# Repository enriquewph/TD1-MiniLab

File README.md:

# TD1-MiniLab
Practico de Laboratorio N° 1. --- Mini Lab ---

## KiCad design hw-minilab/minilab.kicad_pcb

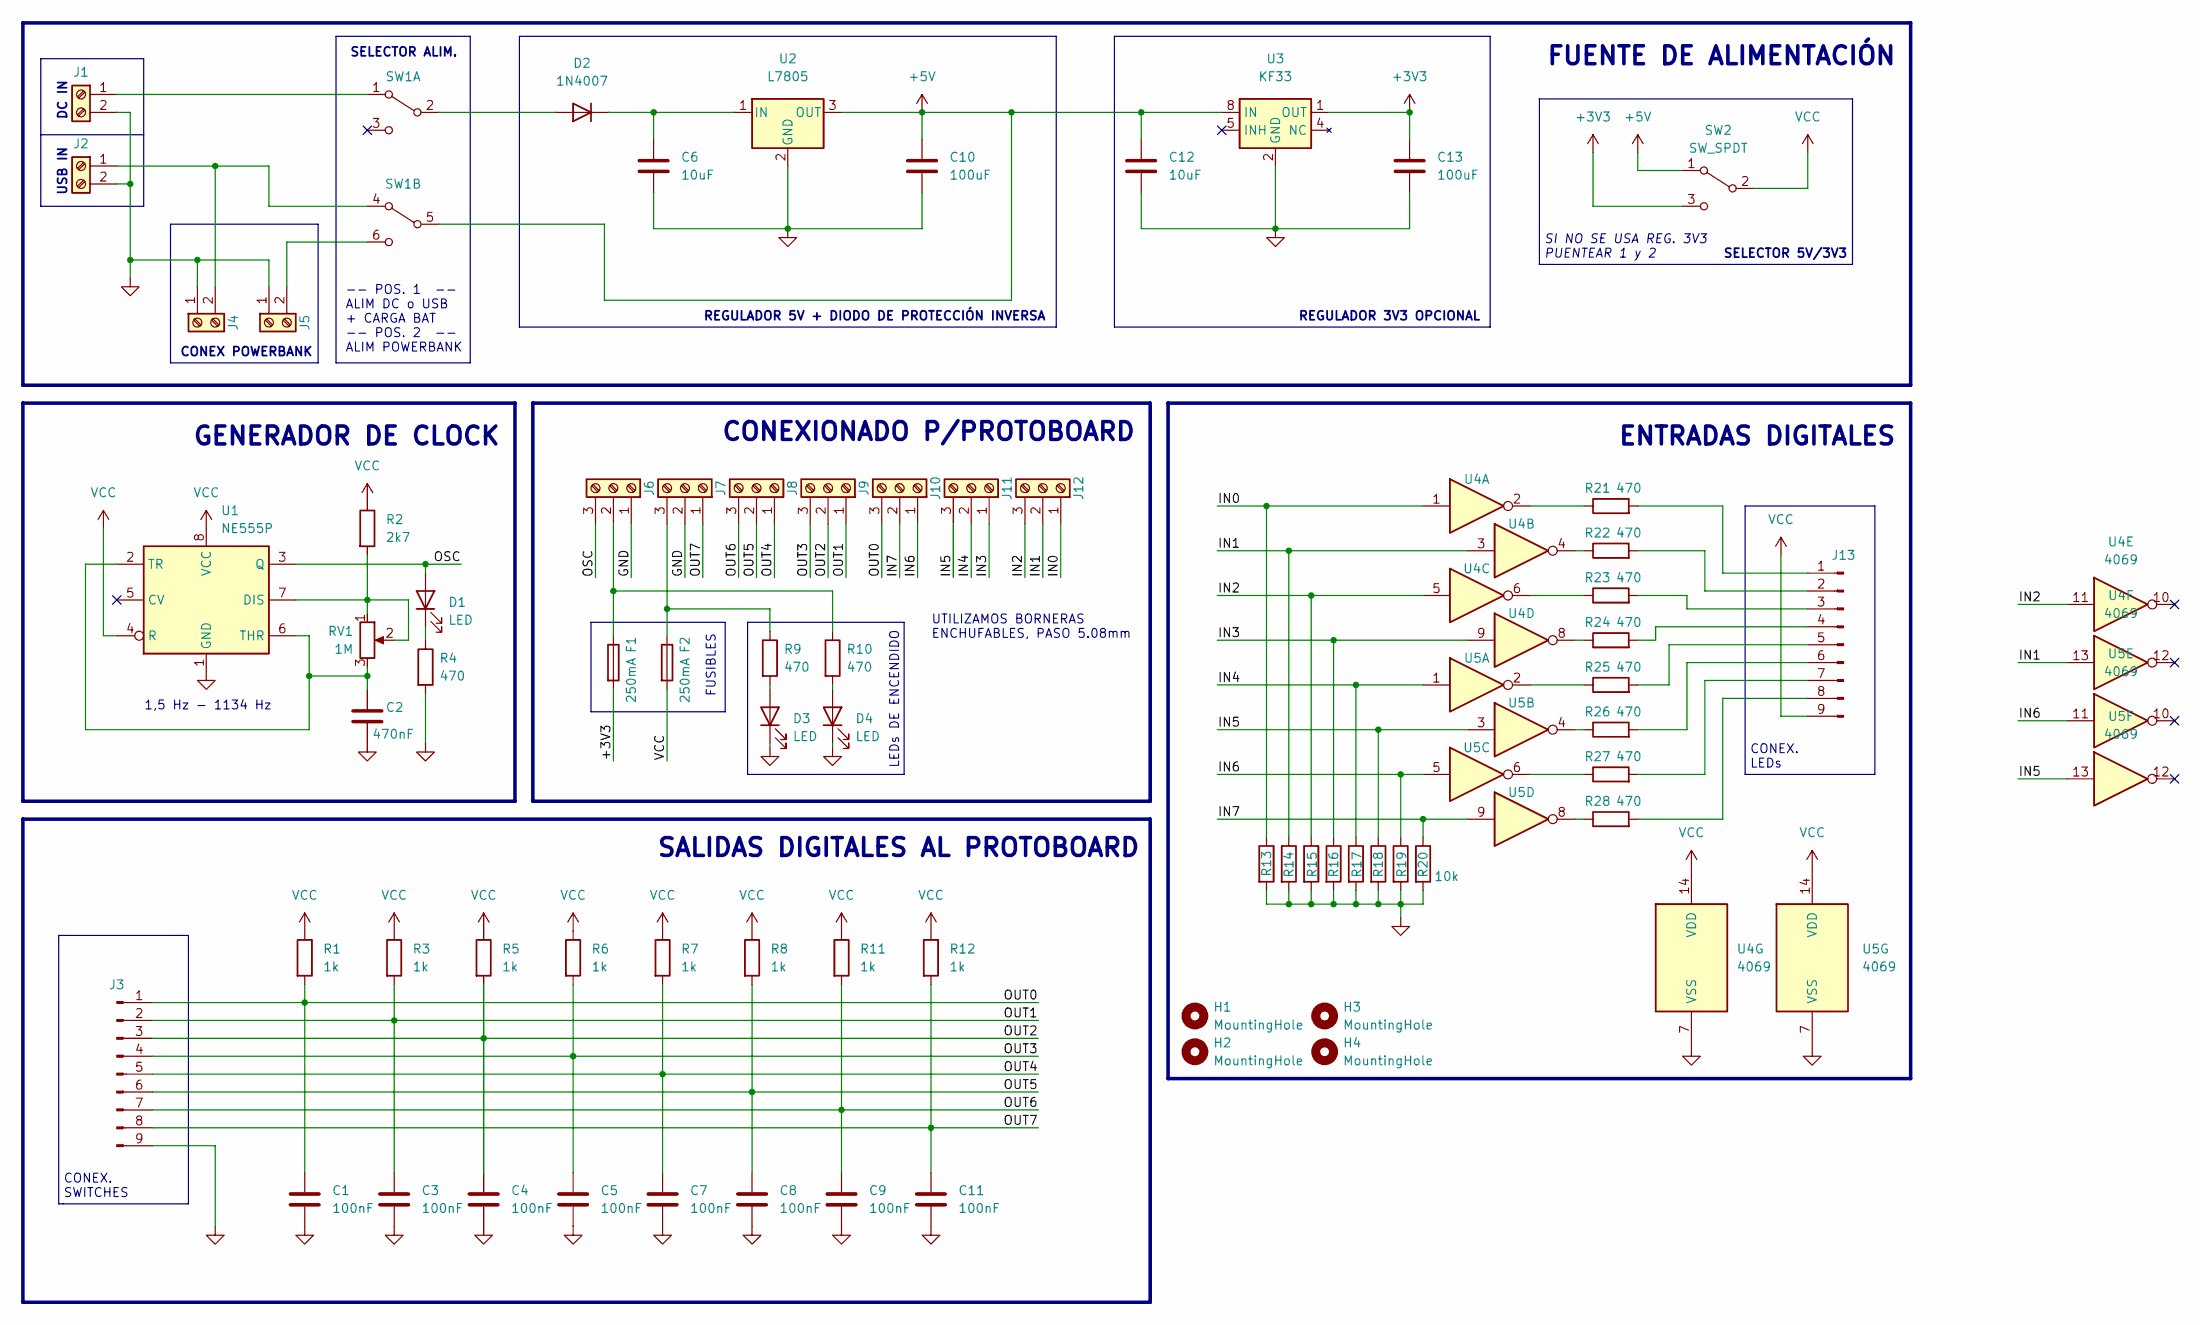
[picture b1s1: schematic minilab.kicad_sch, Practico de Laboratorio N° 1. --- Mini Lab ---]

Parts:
C1, C3, C4, C5, C7, C8, C9, C11: 100nF; C_Disc_D5.0mm_W2.5mm_P5.00mm
C2: 470nF; C_Disc_D5.0mm_W2.5mm_P5.00mm
C6, C12: 10uF; C_Disc_D5.0mm_W2.5mm_P2.50mm
C10, C13: 100uF; C_Disc_D5.0mm_W2.5mm_P2.50mm
D1, D3, D4: LED; PinHeader_1x02_P2.54mm_Vertical
D2: 1N4007; D_DO-41_SOD81_P10.16mm_Horizontal
F1, F2: 250mA; TestPoint_2Pads_Pitch5.08mm_Drill1.3mm
H1, H2, H3, H4: MountingHole; MountingHole_3.2mm_M3
J1, J2, J4, J5: Screw_Terminal_01x02; TestPoint_2Pads_Pitch5.08mm_Drill1.3mm
J3, J13: Conn_01x09_Male; PinHeader_1x09_P2.54mm_Vertical
J6, J7, J8, J9, J10, J11, J12: Screw_Terminal_01x03; TerminalBlock_RND_205-00288_1x03_P5.08mm_Horizontal
R1, R3, R5, R6, R7, R8, R11, R12: 1k; R_Axial_DIN0207_L6.3mm_D2.5mm_P7.62mm_Horizontal
R2: 2k7; R_Axial_DIN0207_L6.3mm_D2.5mm_P7.62mm_Horizontal
R4, R9, R10, R21, R22, R23, R24, R25, R26, R27, R28: 470; R_Axial_DIN0207_L6.3mm_D2.5mm_P7.62mm_Horizontal
R13, R14, R15, R16, R17, R18, R19, R20: 10k; R_Axial_DIN0207_L6.3mm_D2.5mm_P7.62mm_Horizontal
RV1: 1M; PinHeader_1x03_P2.54mm_Vertical
SW1: SW_DPDT_x2; TestPoint_6Pads_Pitch5.08mm_Drill1.3mm
SW2: SW_SPDT; TestPoint_3Pads_Pitch5.08mm_Drill1.3mm
U1: NE555P; DIP-8_W7.62mm_Socket_LongPads
U2: L7805; TO-220-3_Horizontal_TabUp
U3: KF33; SOIC-8-1EP_3.9x4.9mm_P1.27mm_EP2.29x3mm
U4, U5: 4069

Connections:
+3V3: C13.1, F1.2, SW2.3 (C), U3.1 (OUT)
+5V: C10.1, C12.1, SW1.5 (B), SW2.1 (A), U2.3 (OUT), U3.8 (IN)
/IN0: J12.1, R13.1, U4.1
/IN1: J12.2, R14.1, U4.3, U4.13
/IN2: J12.3, R15.1, U4.5, U4.11
/IN3: J11.1, R16.1, U4.9
/IN4: J11.2, R17.1, U5.1
/IN5: J11.3, R18.1, U5.3, U5.13
/IN6: J10.1, R19.1, U5.5, U5.11
/IN7: J10.2, R20.1, U5.9
/OSC: D1.2 (A), J6.3, U1.3 (Q)
/OUT0: C1.1, J3.1, J10.3, R1.2
/OUT1: C3.1, J3.2, J9.1, R3.2
/OUT2: C4.1, J3.3, J9.2, R5.2
/OUT3: C5.1, J3.4, J9.3, R6.2
/OUT4: C7.1, J3.5, J8.1, R7.2
/OUT5: C8.1, J3.6, J8.2, R8.2
/OUT6: C9.1, J3.7, J8.3, R11.2
/OUT7: C11.1, J3.8, J7.1, R12.2
GND: C1.2, C2.2, C3.2, C4.2, C5.2, C6.2, C7.2, C8.2, C9.2, C10.2, C11.2, C12.2, C13.2, D3.1 (K), D4.1 (K), J1.2, J2.2, J3.9, J4.1, J5.1, J6.1, J7.2, R4.2, R13.2, R14.2, R15.2, R16.2, R17.2, R18.2, R19.2, R20.2, U1.1 (GND), U2.2 (GND), U3.2 (GND), U3.3 (GND), U3.6 (GND), U3.7 (GND), U3.9 (GND), U4.7 (VSS), U5.7 (VSS)
unnamed: C2.1, RV1.3, U1.2 (TR), U1.6 (THR)
unnamed: C6.1, D2.1 (K), U2.1 (IN)
unnamed: D1.1 (K), R4.1
unnamed: D2.2 (A), SW1.2 (B)
unnamed: D3.2 (A), R9.2
unnamed: D4.2 (A), R10.2
unnamed: F1.1, J6.2, R10.1
unnamed: F2.1, J7.3, R9.1
unnamed: J1.1, SW1.1 (A)
unnamed: J2.1, J4.2, SW1.4 (A)
unnamed: J5.2, SW1.6 (C)
unnamed: J13.1, R21.2
unnamed: J13.2, R22.2
unnamed: J13.3, R23.2
unnamed: J13.4, R24.2
unnamed: J13.5, R25.2
unnamed: J13.6, R26.2
unnamed: J13.7, R27.2
unnamed: J13.8, R28.2
unnamed: R2.2, RV1.1, RV1.2, U1.7 (DIS)
unnamed: R21.1, U4.2
unnamed: R22.1, U4.4
unnamed: R23.1, U4.6
unnamed: R24.1, U4.8
unnamed: R25.1, U5.2
unnamed: R26.1, U5.4
unnamed: R27.1, U5.6
unnamed: R28.1, U5.8
VCC: F2.2, J13.9, R1.1, R2.1, R3.1, R5.1, R6.1, R7.1, R8.1, R11.1, R12.1, SW2.2 (B), U1.4 (R), U1.8 (VCC), U4.14 (VDD), U5.14 (VDD)

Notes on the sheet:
SELECTOR 5V/3V3
SALIDAS DIGITALES AL PROTOBOARD
CONEXIONADO P/PROTOBOARD
DC IN
USB IN
UTILIZAMOS BORNERAS ENCHUFABLES, PASO 5.08mm
GENERADOR DE CLOCK
1,5 Hz - 1134 Hz
SI NO SE USA REG. 3V3 PUENTEAR 1 y 2
CONEX. LEDs
CONEX. SWITCHES
ENTRADAS DIGITALES
REGULADOR 5V + DIODO DE PROTECCIÓN INVERSA
LEDs DE ENCENDIDO
REGULADOR 3V3 OPCIONAL
SELECTOR ALIM.
FUSIBLES
-- POS. 1 -- ALIM DC o USB + CARGA BAT -- POS. 2 -- ALIM POWERBANK
FUENTE DE ALIMENTACIÓN
CONEX POWERBANK

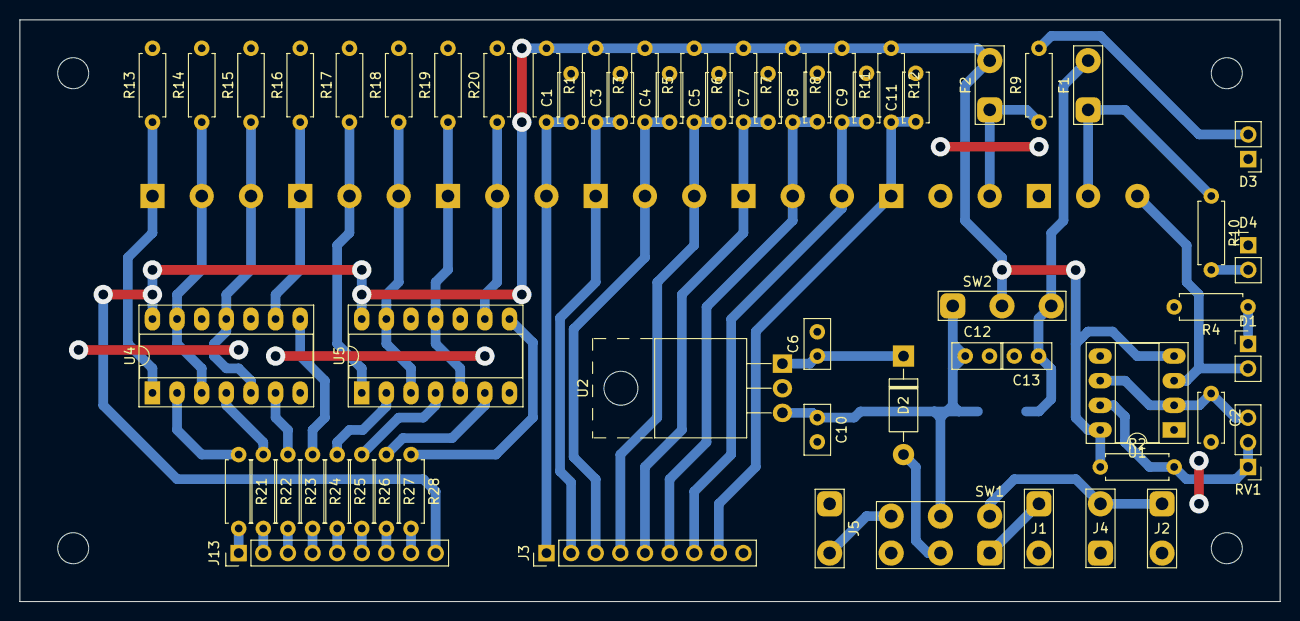
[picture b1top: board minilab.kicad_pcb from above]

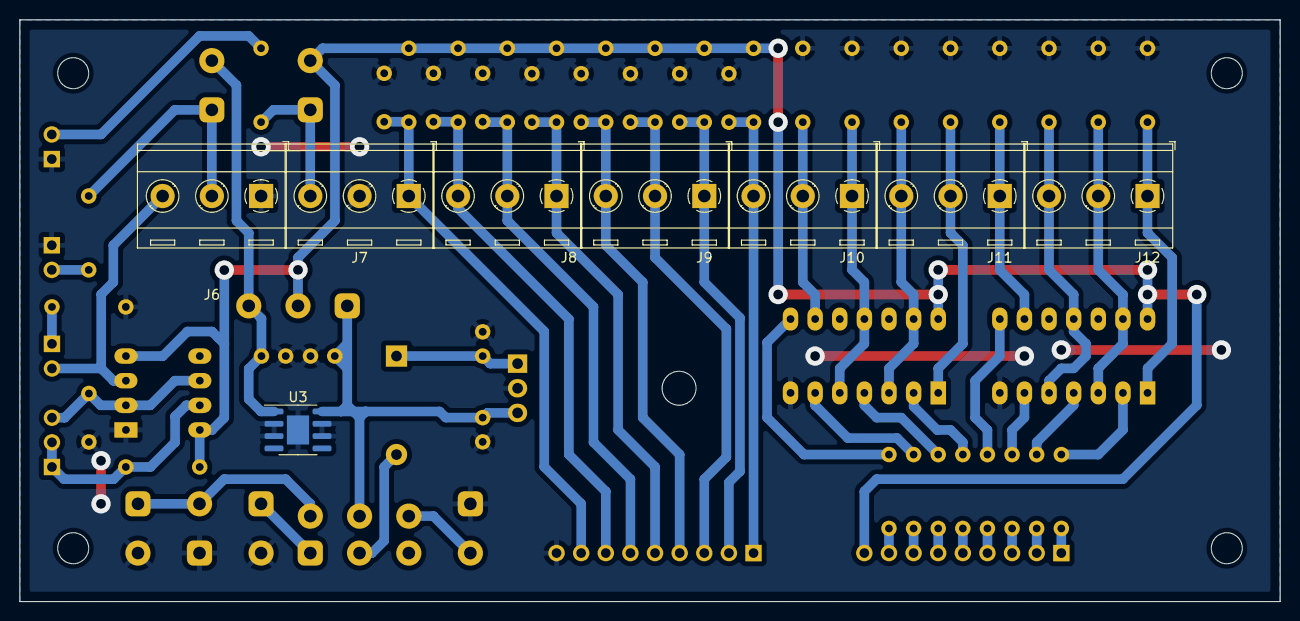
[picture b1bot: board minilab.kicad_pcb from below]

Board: 2 copper layers, 130.0 x 60.0 mm, 72 parts (8 on the bottom side), 49 nets.

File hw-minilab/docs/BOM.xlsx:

Item | Cantidad | Descripción | Valor | Cant. Necesaria Total | Cant. Obtenida | Excedentes | Costo c/u | Costo total | Costo x Minilab
1 | 1 | C. Integrado | NE555P | 4 | 6 | 2 | 209.053845 | 1254.3230699999999 | 313.58076749999998
2 | 1 | C. Integrado | L7805 | 4 | 4 | 0 | 40.840800000000002 | 163.36320000000001 | 40.840800000000002
3 | 1 | C. Integrado | KF33 | 4 | 4 | 0 | 40.840800000000002 | 163.36320000000001 | 40.840800000000002
4 | 2 | C. Integrado | CD4069 | 8 | 12 | 4 | 109.2 | 1310.4000000000001 | 327.60000000000002
5 | 1 | Cap. Cerámico 50V | 470nF | 4 | 4 | 0 | 18.2 | 72.8 | 18.2
6 | 8 | Cap. Cerámico 50V | 100nF | 32 | 32 | 0 | 7 | 224 | 56
7 | 2 | Cap. Electrolítico 16V | 10uF | 8 | 8 | 0 | 3.9131399999999998 | 31.305119999999999 | 7.8262799999999997
8 | 2 | Cap. Electrolítico 16V | 100uF | 8 | 8 | 0 | 3.9131399999999998 | 31.305119999999999 | 7.8262799999999997
9 | 7 | Conector Bornera 3 Pos. 5.08mm | - | 28 | 28 | 0 | 85 | 2380 | 595
10 | 1 | Conector DC Estándar p/gab | - | 4 | 4 | 0 | 100 | 400 | 100
11 | 1 | Diodo Rectificador | 1N4007 | 4 | 4 | 0 | 2.5 | 10 | 2.5
12 | 1 | Disipador TO220 7W | - | 4 | 4 | 0 | 0 | 0 | 0
13 | 7 | Enchufe Bornera 3 Pos. 5.08mm | - | 28 | 28 | 0 | 25 | 700 | 175
14 | 6 | Fusible 20mm | 250mA | 24 | 24 | 0 | 23.8 | 571.20000000000005 | 142.80000000000001
15 | 8 | Imanes Neodimio 5x1mm | - | 32 | 32 | 0 | 36 | 1152 | 288
16 | 8 | LED 5mm Azul | - | 32 | 32 | 0 | 5 | 160 | 40
17 | 3 | LED 5mm Rojo | - | 12 | 12 | 0 | 5 | 60 | 15
18 | 1 | Placa Virgen 20x20 | - | 1 | 1 | 0 | 266 | 266 | 66.5
19 | 2 | Portafusible p/gab | - | 8 | 8 | 0 | 82.6 | 660.8 | 165.2
20 | 1 | Potenciometro p/gabinete | 1M | 4 | 4 | 0 | 138.6 | 554.4 | 138.6
21 | 1 | Power Bank barato 1x18650 | - | 4 | 4 | 0 | 800 | 3200 | 800
22 | 2 | Protoboard 830 puntos | - | 8 | 8 | 0 | 214 | 1712 | 428
23 | 1 | Resistencia 1/4 W | 2k7 | 4 | 50 | 46 | 1.5373049999999997 | 76.865249999999989 | 19.216312499999997
24 | 11 | Resistencia 1/4 W | 470 | 44 | 50 | 6 | 1.5373049999999997 | 76.865249999999989 | 19.216312499999997
25 | 16 | Resistencia 1/4 W | 10k | 64 | 100 | 36 | 1.5373049999999997 | 153.73049999999998 | 38.432624999999994
26 | 9 | Switch Palanca ON/ON | SW_SPDT | 36 | 36 | 0 | 61.492199999999997 | 2213.7192 | 553.4298
27 | 1 | Switch Palanca ON/ON | SW_DPDT | 4 | 4 | 0 | 197.82262500000002 | 791.29050000000007 | 197.82262500000002
28 | 1 | USB Tipo B Hembra | - | 4 | 4 | 0 | 61.261199999999995 | 245.04479999999998 | 61.261199999999995
29 | 2 | Zocalo DIP 14 | - | 8 | 8 | 0 | 10 | 80 | 20
30 | 1 | Zocalo DIP 8 | - | 4 | 4 | 0 | 10 | 40 | 10
31 | 4 | Tornillos M3x20 | - | 16 | 16 | 0 | 20 | 320 | 80
32 | 7 | Tornillos M3x15 | - | 28 | 28 | 0 | 18 | 504 | 126
33 | 4 | Tuercas M3 | - | 16 | 16 | 0 | 2 | 32 | 8
Total |  |  |  |  |  |  |  |  | 4902.6938024999999

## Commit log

2022-03-25 BOM Trabajado en excel
2022-03-26 Switch 3v3 regulator to kf33
2022-03-26 Avances en el routeo
2022-03-26 Add Preliminar STEP output
2022-03-27 Update BOM
2022-03-28 Archivos de fabricacion generados
2022-03-29 Diseños
2022-03-29 Cambios varios, y export para con y sin insertos
2022-04-01 Informe + fix output transfer
2022-04-10 Version entregada
